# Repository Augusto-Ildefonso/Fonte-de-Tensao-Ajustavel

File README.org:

#+title: Projeto de Fonte de Tensão Ajustável
#+author: Marco Túlio, Augusto Ildefonso, Marcelo Caporalli, Lucas Alves

* Fonte de Tensão ajustável

Foi realizado o projeto de uma fonte de tensão ajustável com saída de 3 a 12V, similar a fontes de carregadores de celular. O projeto foi realizado tanto para o aprendizado, como possível reutilização em projetos futuros. O design do circuito foi feito no falstad, com design de PCB no Eagle.

** Componentes
A lista de componentes segue abaixo:
|---------------------------+------------+---------|
| Componente                | Quantidade | Preço   |
|---------------------------+------------+---------|
| Capacitor 1000  \mu F     |          1 | R$ 1.75 |
| Resistor de 3.3 k \Omega  |          1 | R$ 0.07 |
| Resistor de 1 k  \Omega   |          1 | R$ 0.07 |
| Resistor de 4.7 k  \Omega |          1 | R$ 0.07 |
| Resistor de 2.2 k \Omega  |          1 | R$ 0.07 |
| Resistor de 100 \Omega    |          1 | R$ 0.07 |
| Diodo Zener 1N4743        |          1 | R$ 0.49 |
| Potênciometro 10 k        |          1 | R$ 6.79 |
| Ponte de Diodo de 0.7 V   |          1 | R$ 3.78 |
| Led de Indicação          |          1 | R$ 0.10 |
| Transistor                |          1 | R$ 0.70 |
|---------------------------+------------+---------|

*** Função dos componentes

- Capacitor 1000  \mu  F: Armazena a energia para fornecer uma saída mais estável. Como nossa entrada é corrente alternada, durante o ciclo negativo, o capacitor fornece a energia para a saída. Durante o ciclo positivo, o capacitor é carregado.
- Resistores de 3.3k \Omega e 1k \Omega : Arranjo em série com o potênciometro.
- Resistor de 4.7k \Omega: Limita a corrente que passa pelo LED indicador.
- Resistor de 2.2k \Omega: Limita a corrente que passa pelo diodo zener.
- Resistor de 100 \Omega: Proteção do Transistor.
- Diodo Zener 1N4743: Regula a tensão de saída.
- Potênciometro 10k: Ajusta a tensão de saída.
- Ponte de Diodo de 0.7V: Transforma a corrente alternada em corrente contínua.
- Led de Inicação: Indica que a fonte está ligada.
- Transistor: Regula a corrente que passa pelo diodo zener.

** Circuito
O circuito foi desenhado no falstad, e pode ser acessado [[https://tinyurl.com/3m72w95a][aqui]]. A imagem do circuito segue abaixo:

#+ATTR_HTML: :width 500
[[file:./Figs/circuito_fals.png]]

** Cálculos
#+ATTR_HTML: :width 500
[[file:./Figs/calculo_capacitor.jpeg]]

** Design Eagle
O design do circuito no Eagle segue abaixo
[[./Figs/eagle.png]]
** PCB
O design do PCB foi feito no Eagle, e pode ser visto abaixo
[[./Figs/pcb.png]]

** Vídeo de Funcionamento
O vídeo de funcionamento pode ser acessado pelo seguinte link: [[https://youtu.be/-I7VpTSj-us][Projeto da Fonte de Tensão Ajustável]]
*** Observação
É importante notar que os valores de tensão variaram para menos, não chegando a 12 V. Isso pode ser devido a uma série de fatores, como a resistência interna dos componentes, como zenner, transistor e até mesmo dos fios. Ademais, o projeto foi feito numa protoboard, não sendo soldado, isso faz com que tenha uma resistência maior, influenciando na tensão de saída.

* Alunos
Os alunos que realizaram o projeto foram:
 - Augusto Fernandes Ildefonso ([[https://github.com/Augusto-Ildefonso][Github]])
 - Lucas Alves da Silva ()
 - Marcelo Caporalli Filho ([[https://github.com/MarceloCFilho][Github]])
 - Marco Túlio Mello Silva ([[https://github.com/Marco-Normal][Github]])

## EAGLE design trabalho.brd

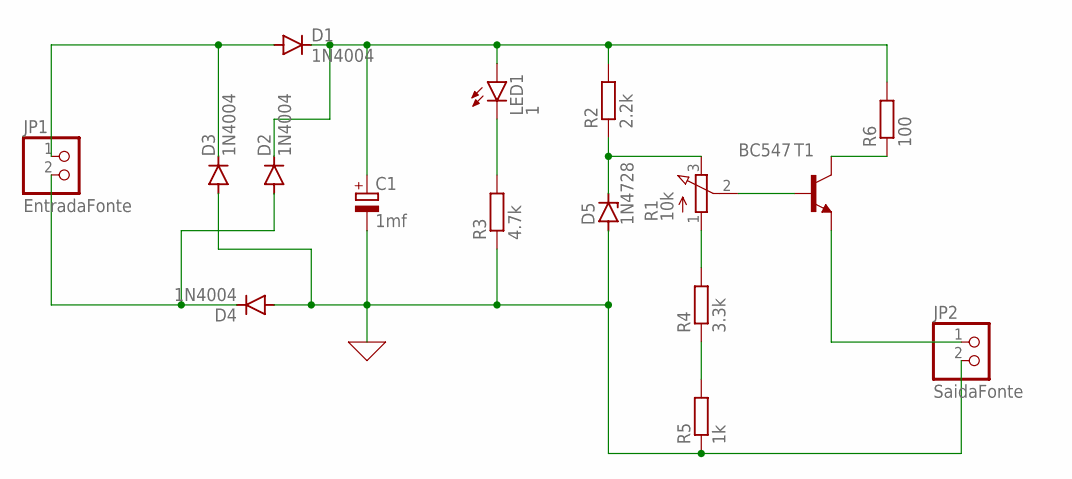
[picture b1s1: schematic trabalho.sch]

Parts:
C1: 1mf; E5-10,5
D1, D2, D3, D4: 1N4004; DO41-10
D5: 1N4728; DO41Z10
JP1: EntradaFonte; 1X02
JP2: SaidaFonte; 1X02
LED1: 1; LED5MM
R1: 10k; 3RP/1610N
R2: 2.2k; 0207/10
R3: 4.7k; 0207/10
R4: 3.3k; 0207/10
R5: 1k; 0207/10
R6: 100; 0207/10
T1: BC547; TO92

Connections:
0: C1.-, D3.A, D4.A, D5.A, JP2.2, R3.1, R5.1
unnamed: C1.+, D1.C, D2.C, LED1.A, R2.2, R6.2
unnamed: LED1.K (C), R3.2
unnamed: D5.C, R1.3 (E), R2.1
unnamed: R1.1 (A), R4.2
unnamed: R4.1, R5.2
unnamed: R1.2 (S), T1.2 (B)
unnamed: R6.1, T1.3 (C)
unnamed: JP2.1, T1.1 (E)
unnamed: D1.A, D3.C, JP1.1
unnamed: D2.A, D4.C, JP1.2

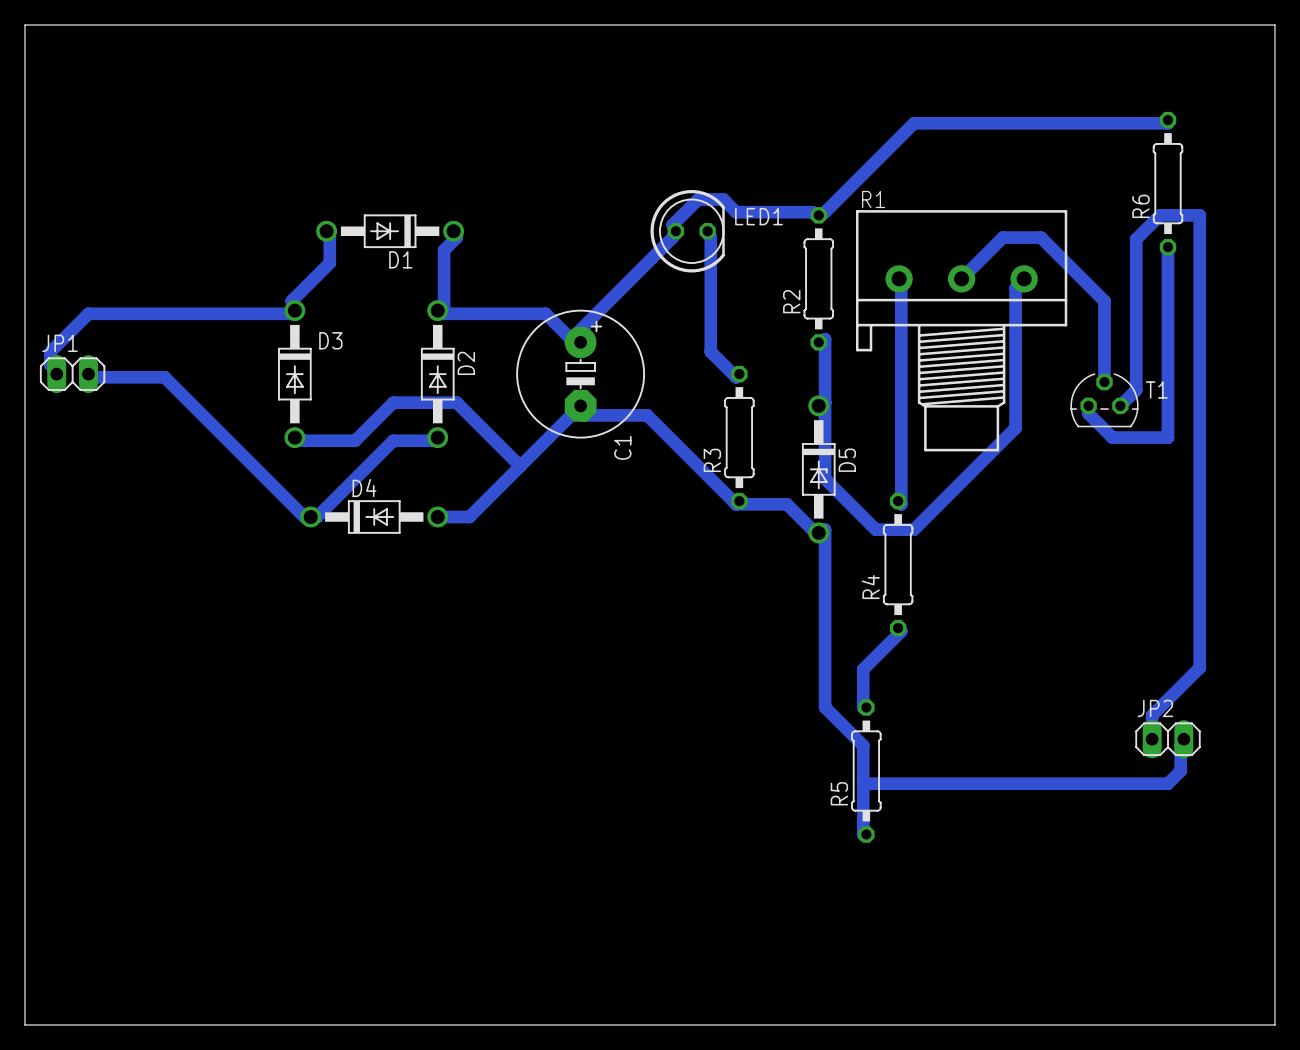
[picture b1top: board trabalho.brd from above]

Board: 2 copper layers, 100.0 x 80.0 mm, 16 parts (0 on the bottom side), 11 nets.

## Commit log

2024-06-18 Upload do arquivo, no falstad, da fonte
2024-06-18 Readme
2024-06-18 Ajustes no README
2024-06-23 Update no Readme e arquivo da fonte
2024-06-23 Troca de Imagem
2024-06-23 Troca Certa de imagem
2024-06-23 Agora imagem certa
2024-06-23 Link para o projeto
2024-06-23 Arrumando Ortografia
2024-06-24 Adicionando foto dos cálculos do capacitor
2024-06-24 Adicionando foto dos cálculos
2024-06-24 Adicionando cálculo do capacitor
2024-06-24 Arrumando imagem dos cálculos
2024-07-02 Imagens
2024-07-06 Adicionando arquivos do esquemático e design do PCB
